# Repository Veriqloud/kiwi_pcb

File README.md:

# kiwi_pcb

Source code for the printed circuit boards. Open with KiCad. 

Contributing
------------

Please check out our [contributing guide](CONTRIBUTING.md) if you're interested in contributing.

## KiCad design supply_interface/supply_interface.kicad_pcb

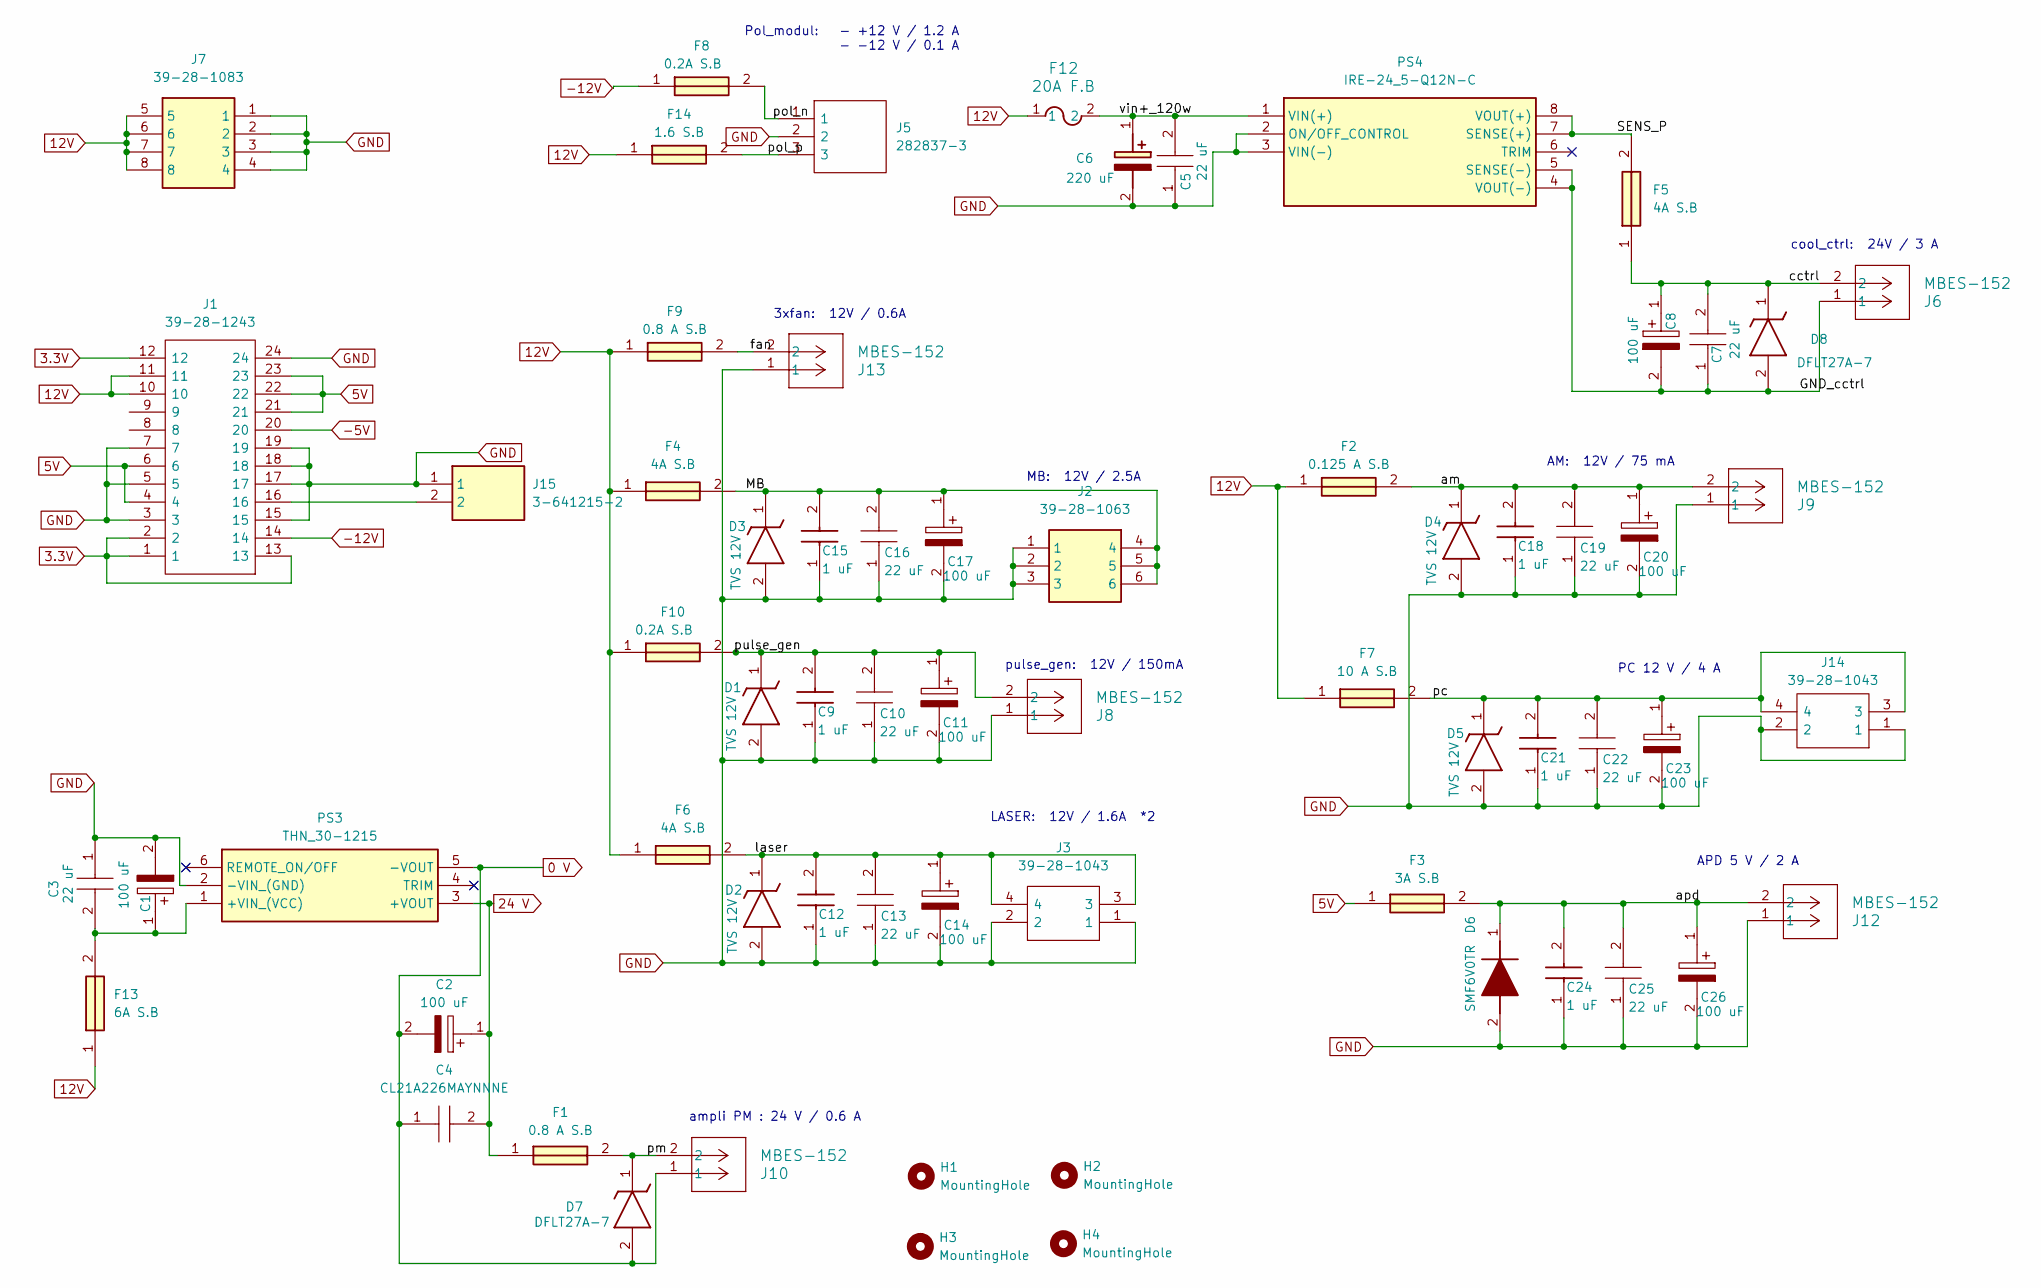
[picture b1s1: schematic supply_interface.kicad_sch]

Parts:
C1, C2, C8, C11, C14, C17, C20, C23, C26: 100 uF; CAPPM7343X310N; Manufacturer_Part_Number T55D107M025C0060; Mouser Part Number 74-T55D107M025C0060
C3, C5, C7, C10, C13, C16, C19, C22, C25: 22 uF; CAPC2012X145N; Mouser Part Number 187-CL21A226MAYNNNE
C4: CL21A226MAYNNNE; CAPC2012X145N; Mouser Part Number 187-CL21A226MAYNNNE
C6: 220 uF; CAPAE1050X1050N; Mouser Part Number 594-MAL215097001E3
C9, C12, C15, C18, C21, C24: 1 uF; GRM15x; Mouser Part Number 81-GRM155R6YA105ME1J
D1, D2, D3, D4, D5: TVS 12V; SODFL3718X130N; Mouser Part Number 750-ATV02W150-HF
D6: SMF6V0TR; Mouser Part Number 755-SMF6V0TR
D7, D8: DFLT27A-7; DFLT27A7; Mouser Part Number 621-DFLT27A-7
F1: 0.8 A S.B; FUSC1608X55N; Mouser Part Number 652-SF-0603S100-2
F2: 0.125 A S.B; 3403015724; Mouser Part Number 693-3403.0157.24
F3: 3A S.B; FUSC3116X70N; Mouser Part Number 652-SF-1206S300-2
F4, F6: 4A S.B; FUSC1005X61N; Mouser Part Number 652-SF-0402S400M-2
F5: 4A S.B; FUSC1608X55N; Mouser Part Number 652-SF-0603S400-2
F7: 10 A S.B; FUSC3216X90N; Mouser Part Number 652-SF-1206S1000R-2
F8, F10: 0.2A S.B; 0ABA0200TN; Manufacturer_Part_Number 0ABA-0200-TN
F9: 0.8 A S.B; FUSC1608X55N; Manufacturer_Part_Number SF-0603SP080-2; Mouser Part Number 652-SF-0603SP080-2
F12: 20A F.B; FUS_CB_3216FF
F13: 6A S.B; FUSC1608X95N; Mouser Part Number 652-SF-0603SA600M-2
F14: 1.6 S.B; FUSC1608X55N; Manufacturer_Part_Number SF-0603S160-2
H1, H2, H3, H4: MountingHole; MountingHole_3mm_Pad_Via
J1: 39-28-1243; Mouser Part Number 538-39-28-1243
J2: 39-28-1063; Mouser Part Number 538-39-28-1063
J3, J14: 39-28-1043; Mouser Part Number 538-39-28-1043
J5: 282837-3; 2828373; Mouser Part Number 571-2828373
J6, J8, J9, J10, J12, J13: MBES-152; CONN_MBES-152_ALT
J7: 39-28-1083; Mouser Part Number 538-39-28-1083
J15: 3-641215-2; SHDR2W66P0X254_1X2_508X572X813P; Mouser Part Number 571-3-641215-2
PS3: THN_30-1215; THN302415; Mouser Part Number 495-THN30-1215
PS4: IRE-24_5-Q12N-C; IRE245Q12NC; Mouser Part Number 580-IRE-24/5-Q12N-C

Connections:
0 V: C2.2, C4.1, D7.2 (A), J10.1, PS3.5 (-VOUT)
3.3V: J1.1, J1.2, J1.12, J1.13
5V: F3.1, J1.4, J1.6, J1.21, J1.22, J1.23
12V: F2.1, F4.1, F6.1, F7.1, F9.1, F10.1, F12.1, F13.1, F14.1, J1.10, J1.11, J7.5, J7.6, J7.7, J7.8
24 V: C2.1, C4.2, F1.1, PS3.3 (+VOUT)
-5V: J1.20
-12V: F8.1, J1.14
/GND_cctrl: C7.1, C8.2, D8.2 (A), J6.1, PS4.4 (VOUT(-)), PS4.5 (SENSE(-))
/MB: C15.2, C16.2, C17.1, D3.1 (K), F4.2, J2.4, J2.5, J2.6
/SENS_P: F5.2, PS4.7 (SENSE(+)), PS4.8 (VOUT(+))
/am: C18.2, C19.2, C20.1, D4.1 (K), F2.2, J9.2
/apd: C24.2, C25.2, C26.1, D6.1 (K), F3.2, J12.2
/cctrl: C7.2, C8.1, D8.1 (K), F5.1, J6.2
/fan: F9.2, J13.2
/laser: C12.2, C13.2, C14.1, D2.1 (K), F6.2, J3.3, J3.4
/pc: C21.2, C22.2, C23.1, D5.1 (K), F7.2, J14.3, J14.4
/pm: D7.1 (K), F1.2, J10.2
/pol_n: F8.2, J5.1
/pol_p: F14.2, J5.3
/pulse_gen: C9.2, C10.2, C11.1, D1.1 (K), F10.2, J8.2
/vin+_120w: C5.2, C6.1 (+), F12.2, PS4.1 (VIN(+))
GND: C1.2, C3.1, C5.1, C6.2 (-), C9.1, C10.1, C11.2, C12.1, C13.1, C14.2, C15.1, C16.1, C17.2, C18.1, C19.1, C20.2, C21.1, C22.1, C23.2, C24.1, C25.1, C26.2, D1.2 (A), D2.2 (A), D3.2 (A), D4.2 (A), D5.2 (A), D6.2 (A), J1.3, J1.5, J1.7, J1.15, J1.17, J1.18, J1.19, J1.24, J2.1, J2.2, J2.3, J3.1, J3.2, J5.2, J7.1, J7.2, J7.3, J7.4, J8.1, J9.1, J12.1, J13.1, J14.1, J14.2, J15.1, PS3.2 (-VIN_(GND)), PS4.2 (ON/OFF_CONTROL), PS4.3 (VIN(-))
unnamed: J1.16, J15.2
unnamed: C1.1, C3.2, F13.2, PS3.1 (+VIN_(VCC))

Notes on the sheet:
PC 12 V / 4 A
cool_ctrl: 24V / 3 A
3xfan: 12V / 0.6A
pulse_gen: 12V / 150mA
MB: 12V / 2.5A
Pol_modul: - +12 V / 1.2 A - -12 V / 0.1 A
LASER: 12V / 1.6A *2
AM: 12V / 75 mA
APD 5 V / 2 A
ampli PM : 24 V / 0.6 A

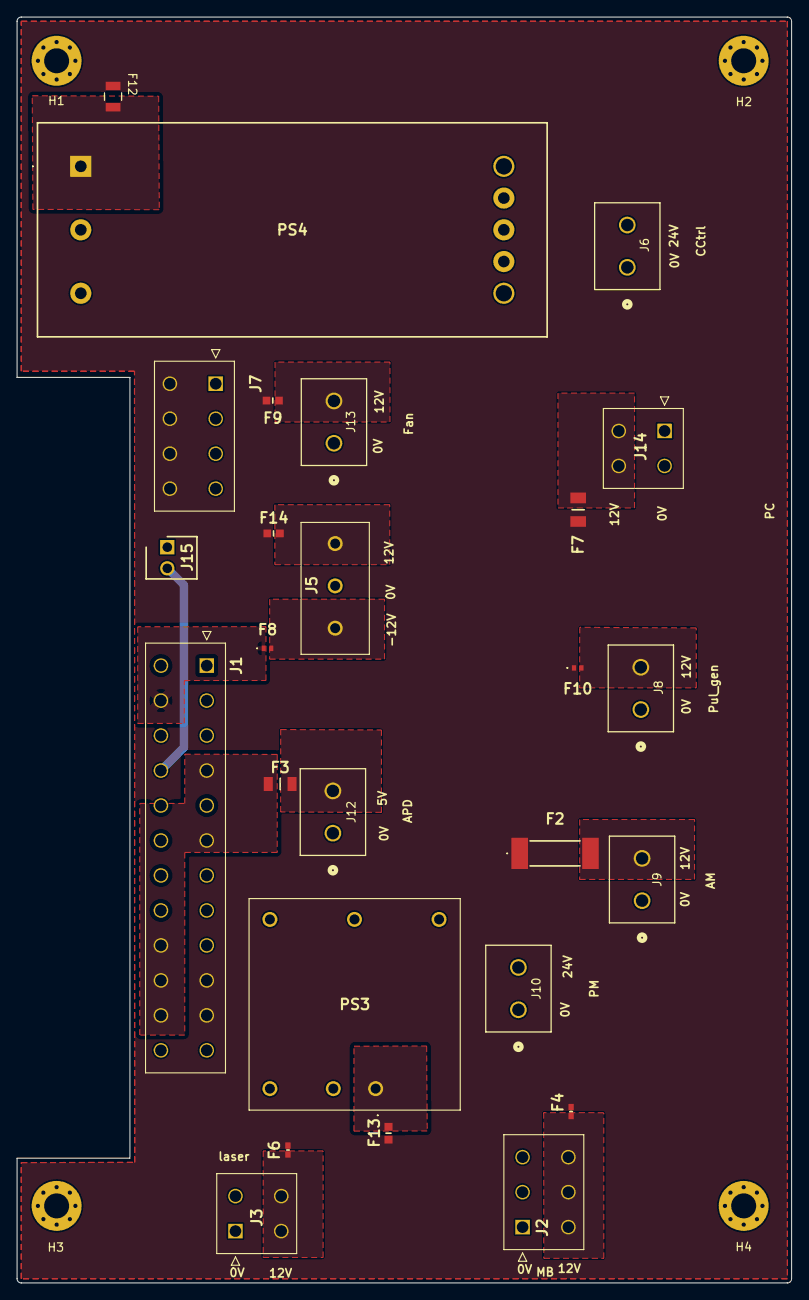
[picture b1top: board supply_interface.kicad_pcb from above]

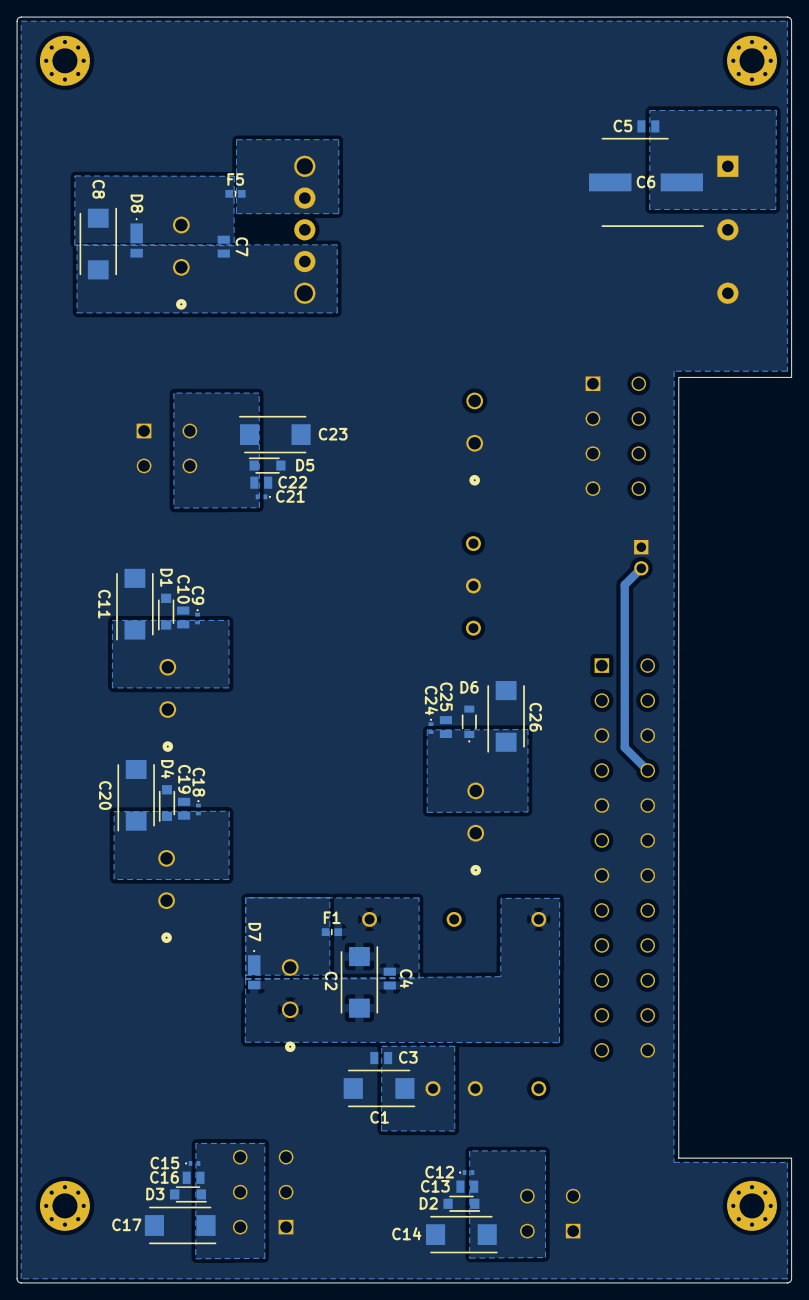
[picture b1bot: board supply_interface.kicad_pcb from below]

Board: 2 copper layers, 93.0 x 152.0 mm, 66 parts (36 on the bottom side), 23 nets.

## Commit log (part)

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2024-12-16 Added libraries
2024-12-16 Added libraries 2
2025-01-17 Create Supply_interface
2025-01-17 add supply_interface PCB design
2025-09-23 added licence
2025-09-27 added sentence in README
2025-10-09 First drafts
2025-10-13 modified contributing.md
2025-11-27 Change folder name
2026-05-29 Update supply interface
2026-06-04 Add TVS protection and decoupling capacitors for power rails
2026-06-04 update ps_on connector
2026-06-11 update2 ps_on connector
2026-06-19 Update PCB files and production outputs
